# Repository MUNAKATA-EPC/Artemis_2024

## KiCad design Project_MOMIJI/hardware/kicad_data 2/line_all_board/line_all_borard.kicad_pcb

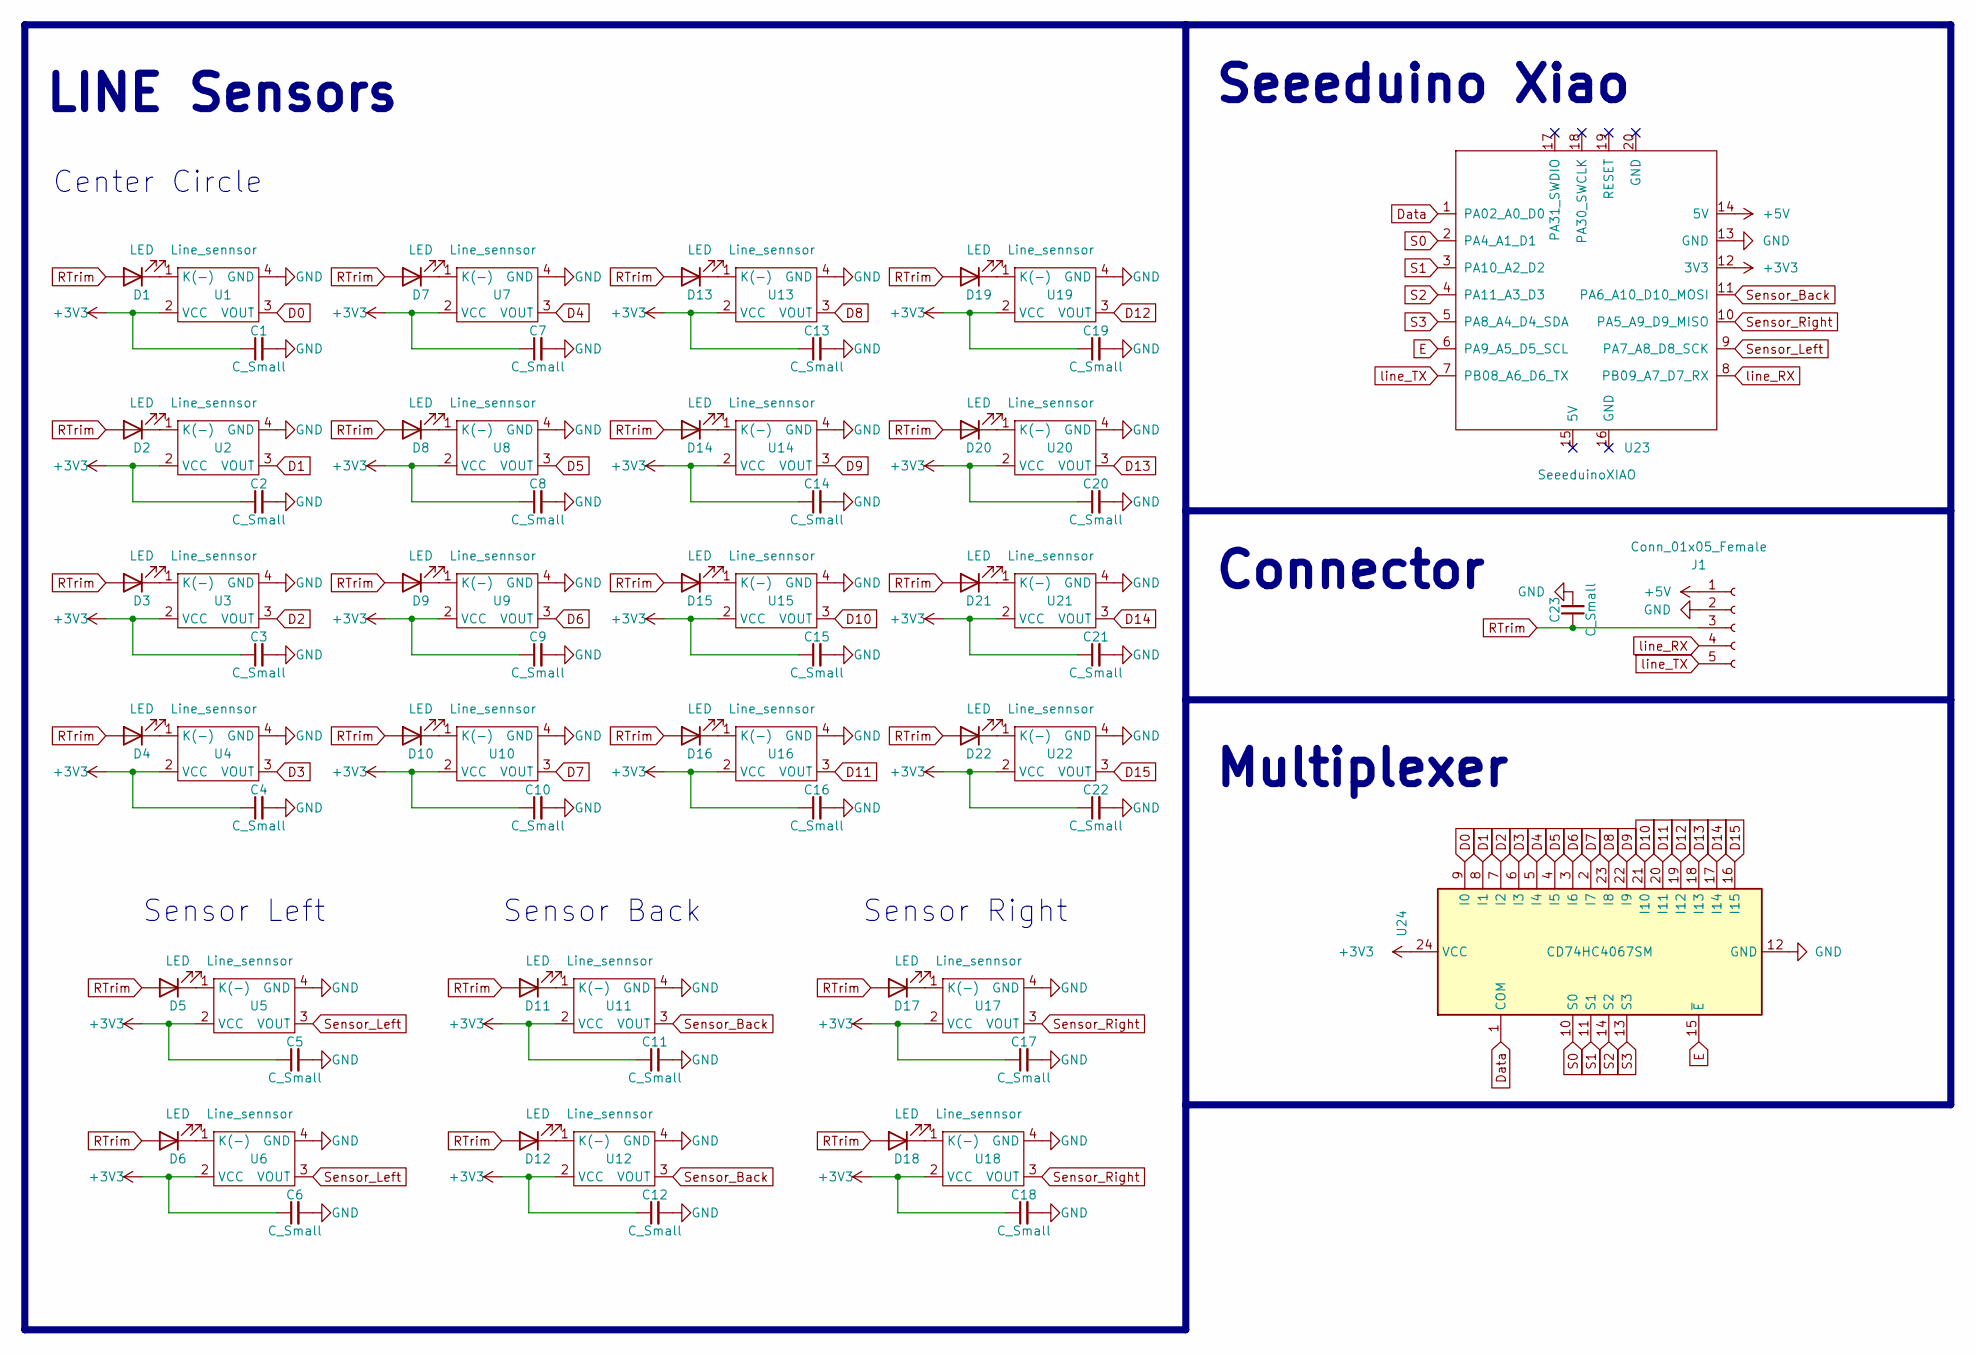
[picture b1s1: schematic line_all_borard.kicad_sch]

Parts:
C1, C2, C3, C4, C5, C6, C7, C8, C9, C10, C11, C12, C13, C14, C15, C16, C17, C18, C19, C20, C21, C22: C_Small; C_Disc_D3.4mm_W2.1mm_P2.50mm
C23: C_Small; CP_Radial_D5.0mm_P2.50mm
D1, D2, D3, D4, D5, D6, D7, D8, D9, D10, D11, D12, D13, D14, D15, D16, D17, D18, D19, D20, D21, D22: LED; LED_D3.0mm
J1: Conn_01x05_Female; JST_XH_B5B-XH-A_1x05_P2.50mm_Vertical
U1, U2, U3, U4, U5, U6, U7, U8, U9, U10, U11, U12, U13, U14, U15, U16, U17, U18, U19, U20, U21, U22: Line_sennsor; Line_Sensor_SMD
U23: SeeeduinoXIAO; seeeduinoXIAO
U24: CD74HC4067SM; SSOP-24_5.3x8.2mm_P0.65mm; LCSC C98457

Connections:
+3V3: C1.1, C2.1, C3.1, C4.1, C5.1, C6.1, C7.1, C8.1, C9.1, C10.1, C11.1, C12.1, C13.1, C14.1, C15.1, C16.1, C17.1, C18.1, C19.1, C20.1, C21.1, C22.1, U1.2 (VCC), U2.2 (VCC), U3.2 (VCC), U4.2 (VCC), U5.2 (VCC), U6.2 (VCC), U7.2 (VCC), U8.2 (VCC), U9.2 (VCC), U10.2 (VCC), U11.2 (VCC), U12.2 (VCC), U13.2 (VCC), U14.2 (VCC), U15.2 (VCC), U16.2 (VCC), U17.2 (VCC), U18.2 (VCC), U19.2 (VCC), U20.2 (VCC), U21.2 (VCC), U22.2 (VCC), U23.12 (3V3), U24.24 (VCC)
+5V: J1.1, U23.14 (5V)
D0: U1.3 (VOUT), U24.9 (I0)
D1: U2.3 (VOUT), U24.8 (I1)
D2: U3.3 (VOUT), U24.7 (I2)
D3: U4.3 (VOUT), U24.6 (I3)
D4: U7.3 (VOUT), U24.5 (I4)
D5: U8.3 (VOUT), U24.4 (I5)
D6: U9.3 (VOUT), U24.3 (I6)
D7: U10.3 (VOUT), U24.2 (I7)
D8: U13.3 (VOUT), U24.23 (I8)
D9: U14.3 (VOUT), U24.22 (I9)
D10: U15.3 (VOUT), U24.21 (I10)
D11: U16.3 (VOUT), U24.20 (I11)
D12: U19.3 (VOUT), U24.19 (I12)
D13: U20.3 (VOUT), U24.18 (I13)
D14: U21.3 (VOUT), U24.17 (I14)
D15: U22.3 (VOUT), U24.16 (I15)
Data: U23.1 (PA02_A0_D0), U24.1 (COM)
E: U23.6 (PA9_A5_D5_SCL), U24.15 (~E)
GND: C1.2, C2.2, C3.2, C4.2, C5.2, C6.2, C7.2, C8.2, C9.2, C10.2, C11.2, C12.2, C13.2, C14.2, C15.2, C16.2, C17.2, C18.2, C19.2, C20.2, C21.2, C22.2, C23.2, J1.2, U1.4 (GND), U2.4 (GND), U3.4 (GND), U4.4 (GND), U5.4 (GND), U6.4 (GND), U7.4 (GND), U8.4 (GND), U9.4 (GND), U10.4 (GND), U11.4 (GND), U12.4 (GND), U13.4 (GND), U14.4 (GND), U15.4 (GND), U16.4 (GND), U17.4 (GND), U18.4 (GND), U19.4 (GND), U20.4 (GND), U21.4 (GND), U22.4 (GND), U23.13 (GND), U24.12 (GND)
unnamed: D1.1 (K), U1.1 (K(-))
unnamed: D2.1 (K), U2.1 (K(-))
unnamed: D3.1 (K), U3.1 (K(-))
unnamed: D4.1 (K), U4.1 (K(-))
unnamed: D5.1 (K), U5.1 (K(-))
unnamed: D6.1 (K), U6.1 (K(-))
unnamed: D7.1 (K), U7.1 (K(-))
unnamed: D8.1 (K), U8.1 (K(-))
unnamed: D9.1 (K), U9.1 (K(-))
unnamed: D10.1 (K), U10.1 (K(-))
unnamed: D11.1 (K), U11.1 (K(-))
unnamed: D12.1 (K), U12.1 (K(-))
unnamed: D13.1 (K), U13.1 (K(-))
unnamed: D14.1 (K), U14.1 (K(-))
unnamed: D15.1 (K), U15.1 (K(-))
unnamed: D16.1 (K), U16.1 (K(-))
unnamed: D17.1 (K), U17.1 (K(-))
unnamed: D18.1 (K), U18.1 (K(-))
unnamed: D19.1 (K), U19.1 (K(-))
unnamed: D20.1 (K), U20.1 (K(-))
unnamed: D21.1 (K), U21.1 (K(-))
unnamed: D22.1 (K), U22.1 (K(-))
RTrim: C23.1, D1.2 (A), D2.2 (A), D3.2 (A), D4.2 (A), D5.2 (A), D6.2 (A), D7.2 (A), D8.2 (A), D9.2 (A), D10.2 (A), D11.2 (A), D12.2 (A), D13.2 (A), D14.2 (A), D15.2 (A), D16.2 (A), D17.2 (A), D18.2 (A), D19.2 (A), D20.2 (A), D21.2 (A), D22.2 (A), J1.3
S0: U23.2 (PA4_A1_D1), U24.10 (S0)
S1: U23.3 (PA10_A2_D2), U24.11 (S1)
S2: U23.4 (PA11_A3_D3), U24.14 (S2)
S3: U23.5 (PA8_A4_D4_SDA), U24.13 (S3)
Sensor_Back: U11.3 (VOUT), U12.3 (VOUT), U23.11 (PA6_A10_D10_MOSI)
Sensor_Left: U5.3 (VOUT), U6.3 (VOUT), U23.9 (PA7_A8_D8_SCK)
Sensor_Right: U17.3 (VOUT), U18.3 (VOUT), U23.10 (PA5_A9_D9_MISO)
line_RX: J1.4, U23.8 (PB09_A7_D7_RX)
line_TX: J1.5, U23.7 (PB08_A6_D6_TX)

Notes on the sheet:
Sensor Right
LINE Sensors
Center Circle
Sensor Left
Sensor Back
Seeeduino Xiao
Connector
Multiplexer

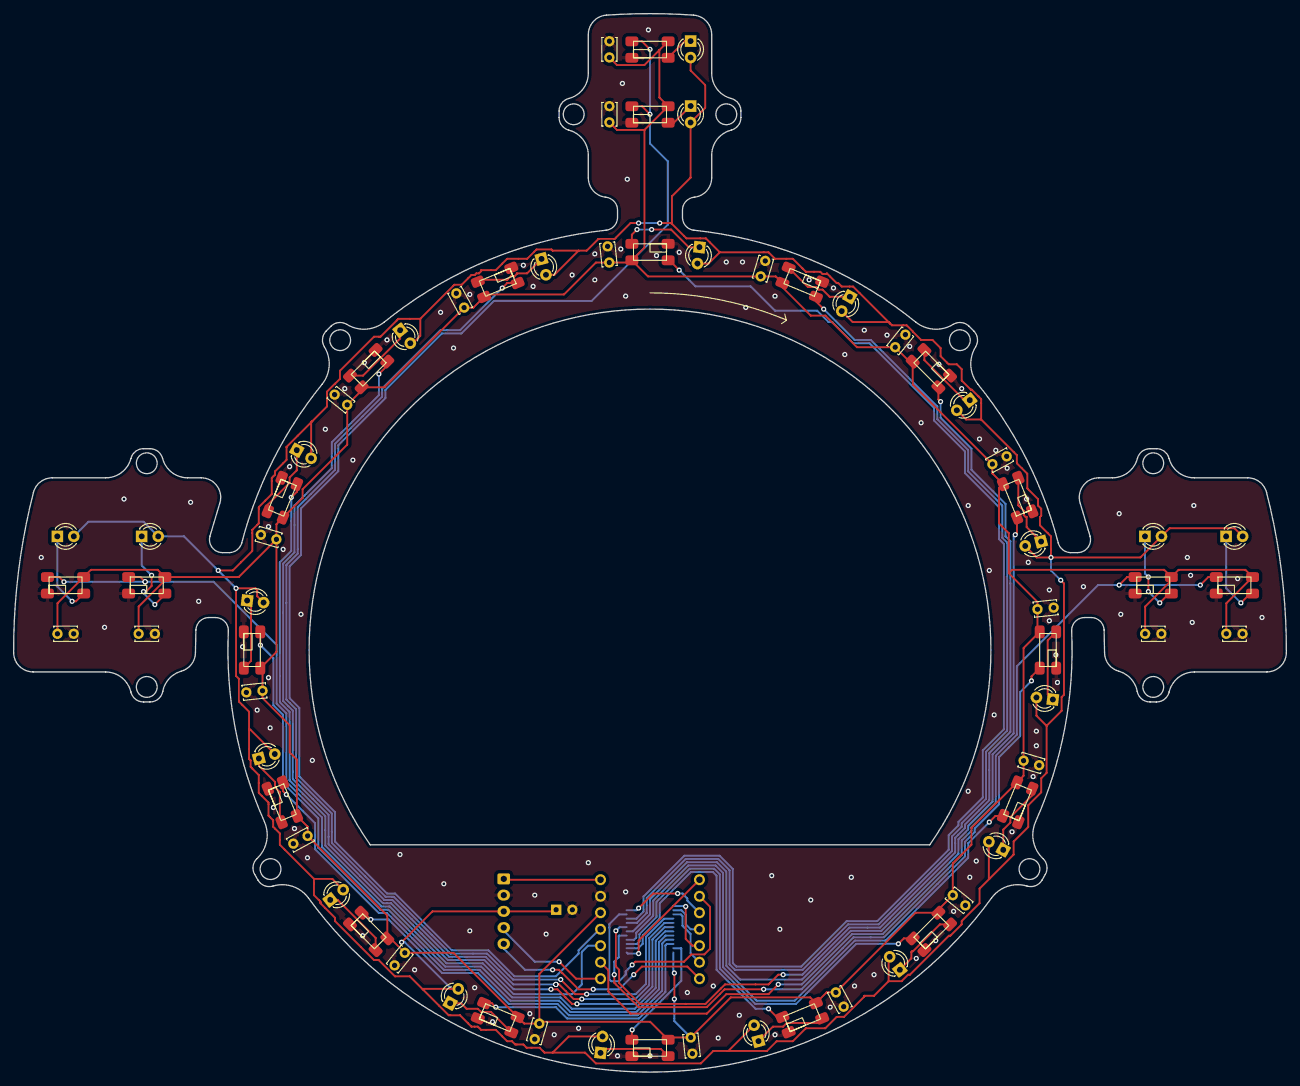
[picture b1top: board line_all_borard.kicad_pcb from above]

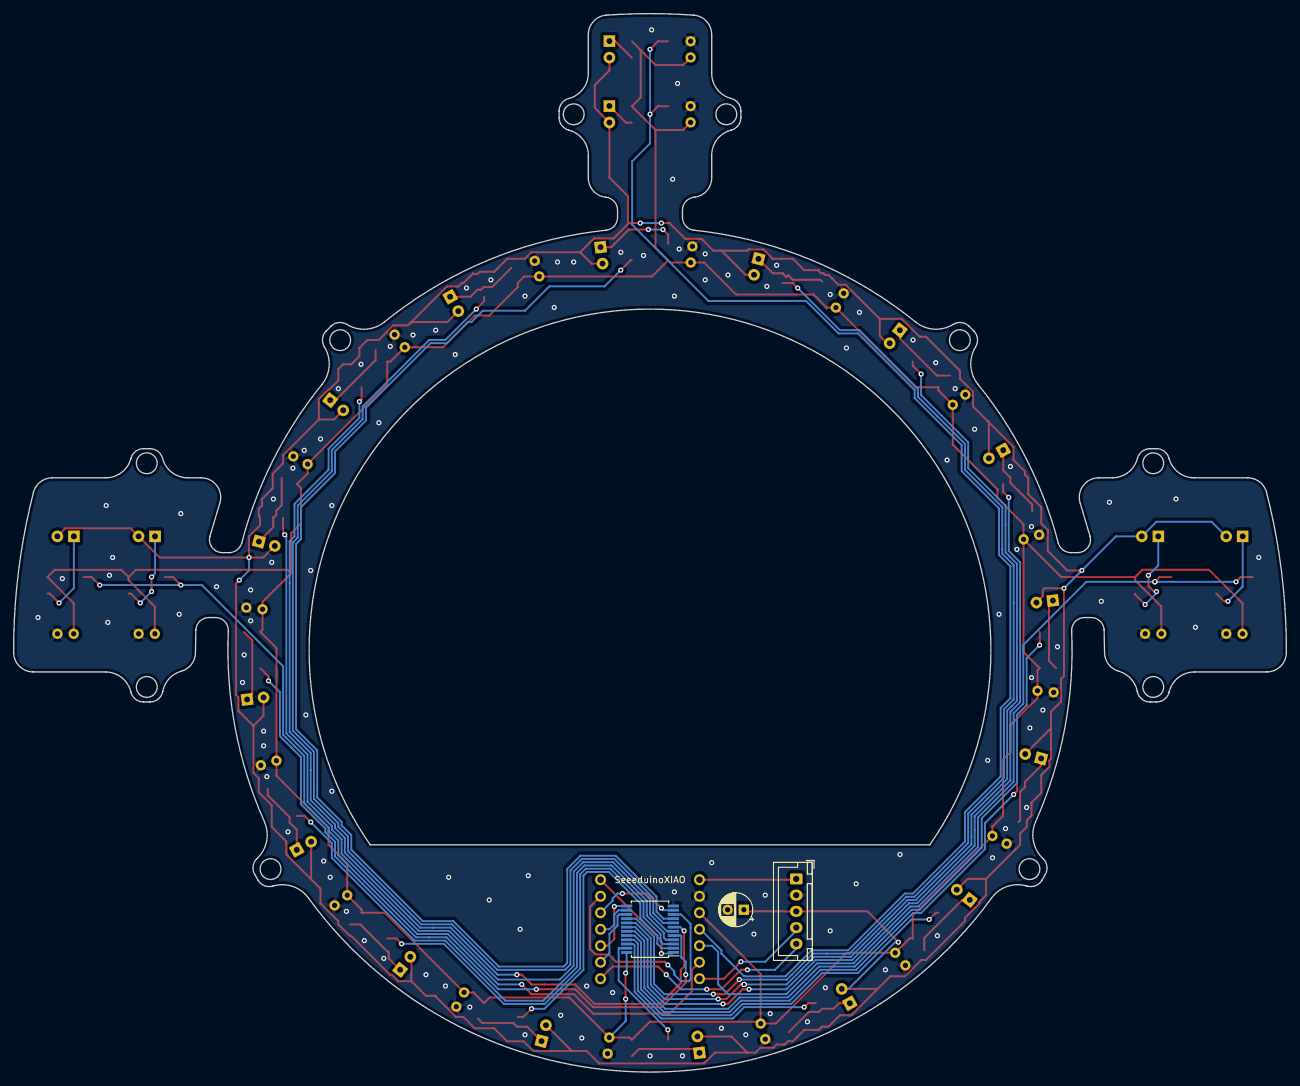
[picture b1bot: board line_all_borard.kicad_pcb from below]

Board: 2 copper layers, 196.0 x 163.0 mm, 70 parts (4 on the bottom side), 53 nets.

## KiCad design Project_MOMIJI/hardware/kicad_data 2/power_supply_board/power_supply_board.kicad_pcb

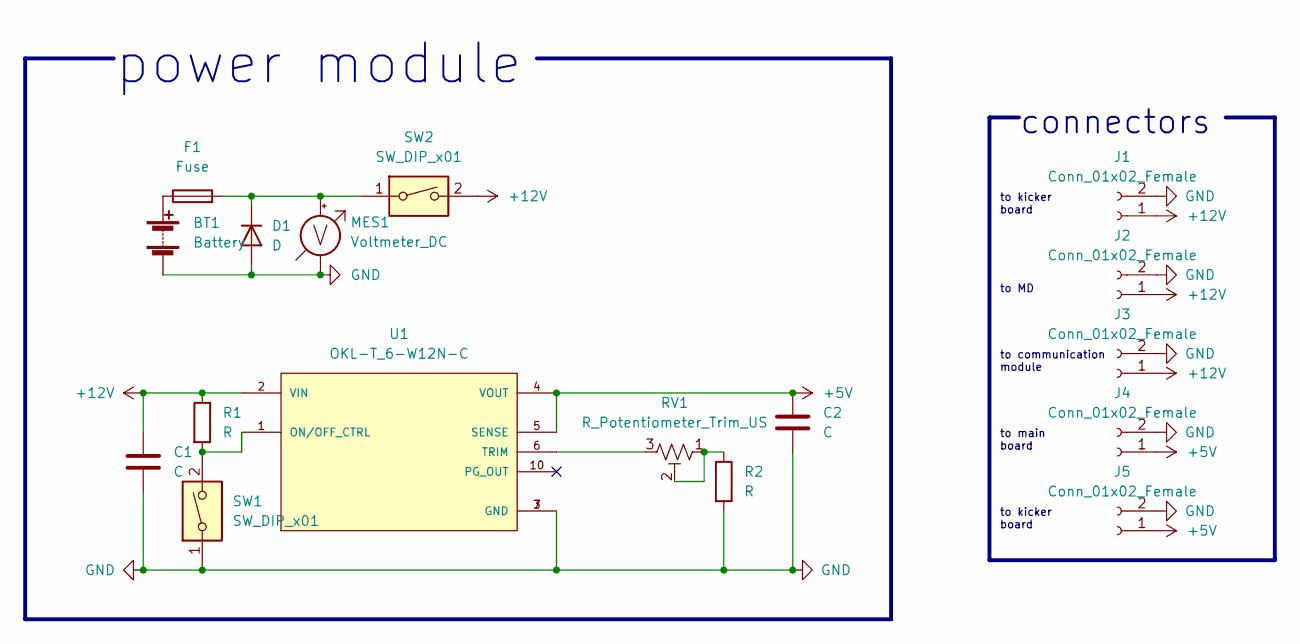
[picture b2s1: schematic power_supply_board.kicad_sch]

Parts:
BT1: Battery; JST_VH_B2P-VH_1x02_P3.96mm_Vertical
C1, C2: C; C_Disc_D4.7mm_W2.5mm_P5.00mm
D1: D; D_A-405_P10.16mm_Horizontal
F1: Fuse; fuse_socket
J1, J2, J3, J4, J5: Conn_01x02_Female; JST_XH_B2B-XH-A_1x02_P2.50mm_Vertical
MES1: Voltmeter_DC; voltage_counter
R1, R2: R; R_Axial_DIN0207_L6.3mm_D2.5mm_P7.62mm_Horizontal
RV1: R_Potentiometer_Trim_US; 2MS1T2B4M2QES
SW1: SW_DIP_x01; SW_S
SW2: SW_DIP_x01; DS-850k
U1: OKL-T_6-W12N-C; DCDC-murata-6A

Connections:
+5V: C2.1, J4.1, J5.1, U1.4 (VOUT), U1.5 (SENSE)
+12V: C1.1, J1.1, J2.1, J3.1, R1.1, SW2.2, U1.2 (VIN)
GND: BT1.2 (-), C1.2, C2.2, D1.2 (A), J1.2, J2.2, J3.2, J4.2, J5.2, MES1.1 (-), R2.2, SW1.1, U1.3 (GND), U1.7 (GND)
unnamed: BT1.1 (+), F1.1
unnamed: D1.1 (K), F1.2, MES1.2 (+), SW2.1
unnamed: R1.2, SW1.2, U1.1 (ON/OFF_CTRL)
unnamed: R2.1, RV1.1, RV1.2
unnamed: RV1.3, U1.6 (TRIM)

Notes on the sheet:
connectors
to communication module
to main board
to MD
to kicker board
power module

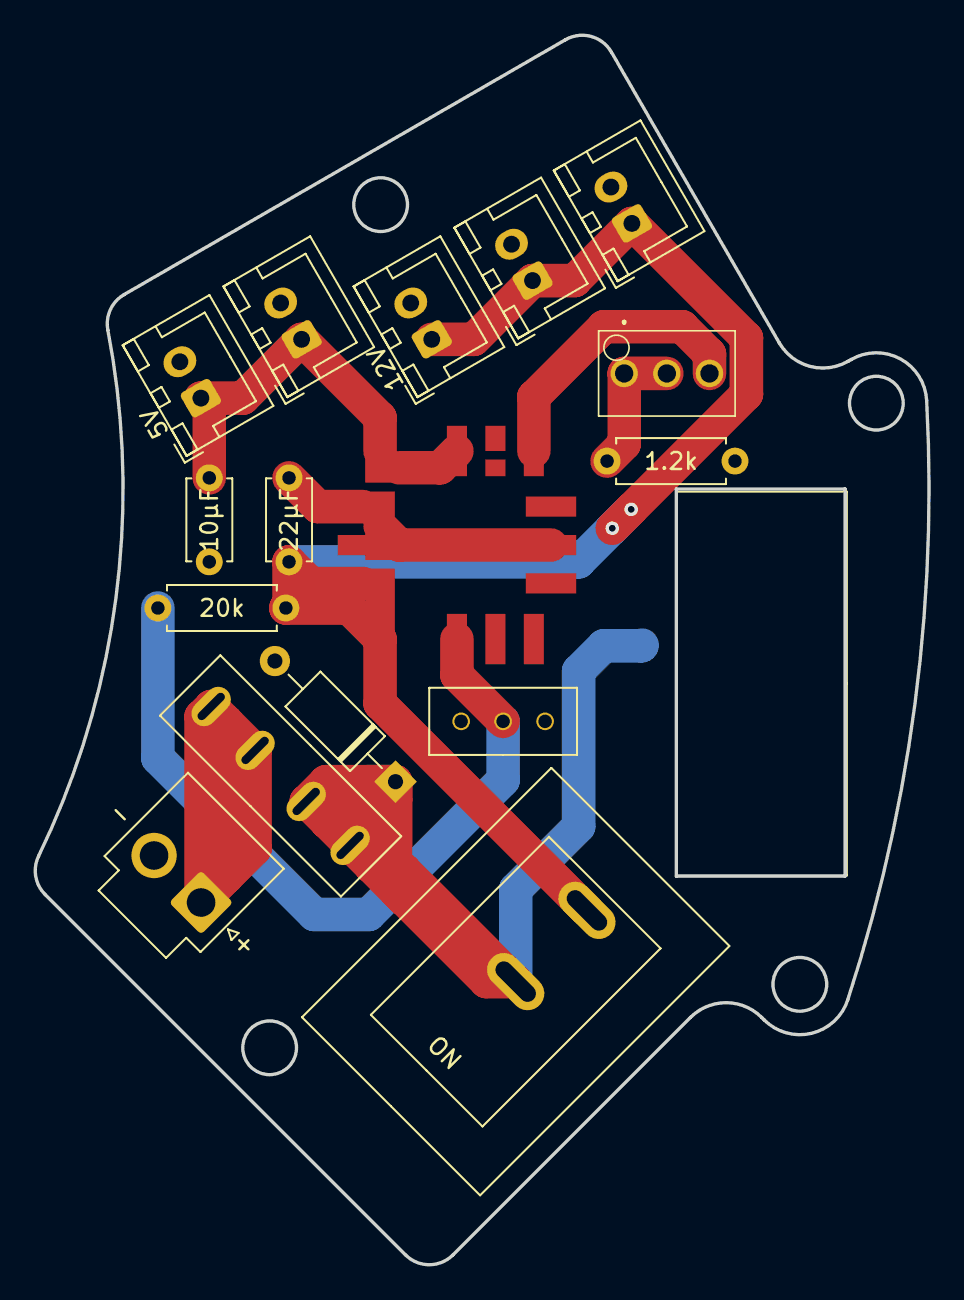
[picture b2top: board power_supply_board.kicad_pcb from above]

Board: 2 copper layers, 53.2 x 73.2 mm, 17 parts (0 on the bottom side), 8 nets.

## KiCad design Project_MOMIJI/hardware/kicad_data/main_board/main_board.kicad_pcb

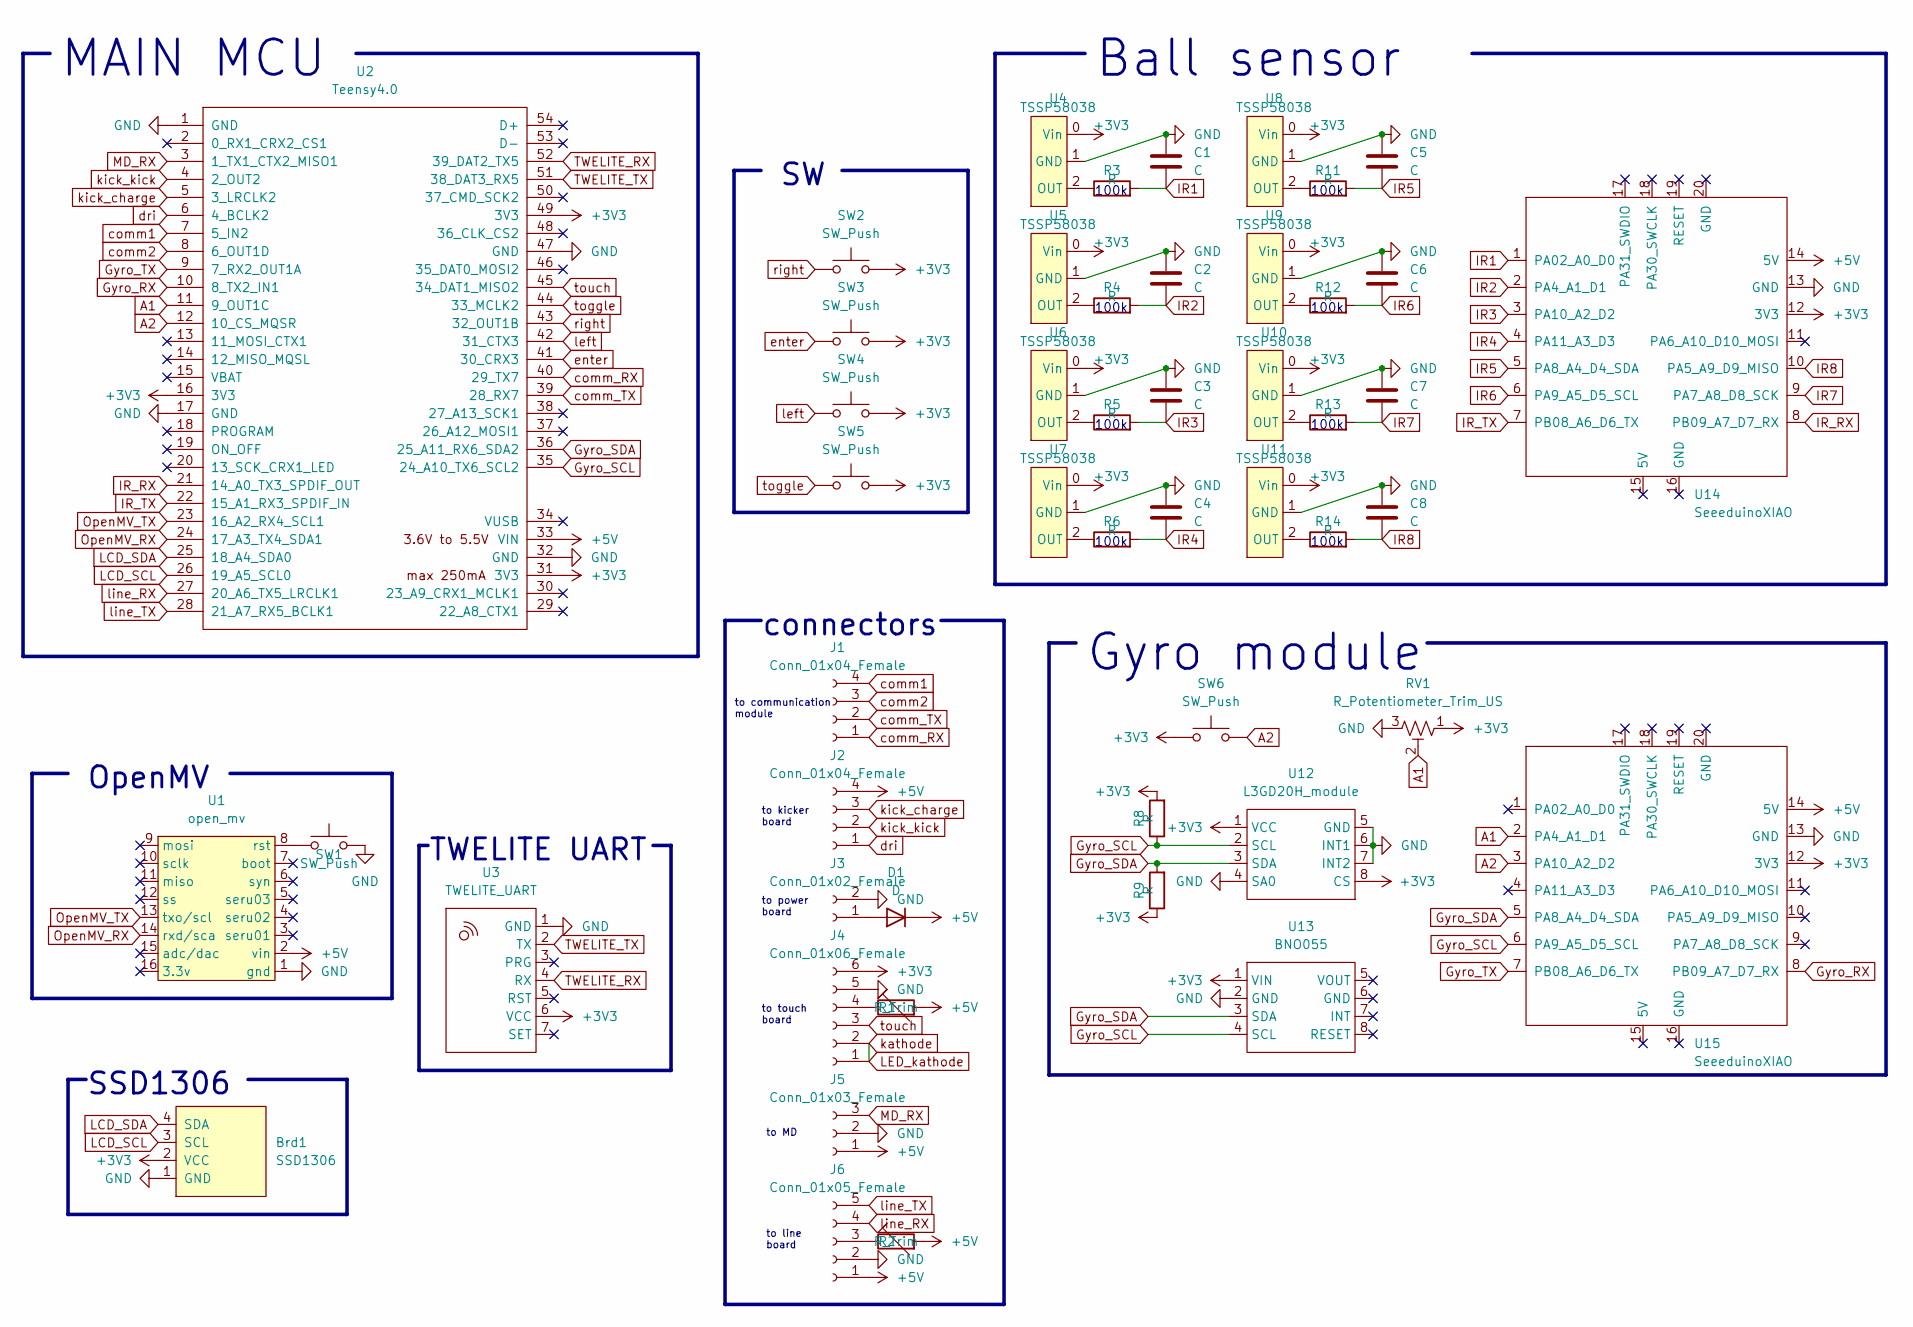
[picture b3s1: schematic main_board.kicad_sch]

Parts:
Brd1: SSD1306; PinSocket_1x04_P2.54mm_Vertical
C1, C2, C3, C4, C5, C6, C7, C8: C; C_Disc_D3.4mm_W2.1mm_P2.50mm
D1: D; D_5W_P12.70mm_Horizontal
J1, J2: Conn_01x04_Female; JST_XH_B4B-XH-A_1x04_P2.50mm_Vertical
J3: Conn_01x02_Female; JST_XH_B2B-XH-A_1x02_P2.50mm_Vertical
J4: Conn_01x06_Female; JST_XH_B6B-XH-A_1x06_P2.50mm_Vertical
J5: Conn_01x03_Female; JST_XH_B3B-XH-A_1x03_P2.50mm_Vertical
J6: Conn_01x05_Female; JST_XH_B5B-XH-A_1x05_P2.50mm_Vertical
R1, R2: R_Trim; 可変抵抗
R3, R4, R5, R6, R8, R9, R11, R12, R13, R14: R; R_Axial_DIN0207_L6.3mm_D2.5mm_P7.62mm_Horizontal
RV1: R_Potentiometer_Trim_US; 可変抵抗
SW1, SW2, SW3, SW4: SW_Push; SW_PUSH_6mm_H7.3mm
SW5: SW_Push; PinHeader_1x02_P2.54mm_Vertical
SW6: SW_Push; SW
U1: open_mv; OpenMV
U2: Teensy4.0; Teensy_Brakeout
U3: TWELITE_UART; TWELITE UART
U4, U5, U6, U7, U8, U9, U10, U11: TSSP58038
U12: L3GD20H_module; L3GD20H_Module_KiCad6.0
U13: BNO055
U14, U15: SeeeduinoXIAO; seeeduinoXIAO

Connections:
+3V3: Brd1.2 (VCC), J4.6, R8.2, R9.1, RV1.1, SW2.2, SW3.2, SW4.2, SW5.2, SW6.1, U2.16 (3V3), U2.31 (3V3), U2.49 (3V3), U3.6 (VCC), U4.0 (Vin), U5.0 (Vin), U6.0 (Vin), U7.0 (Vin), U8.0 (Vin), U9.0 (Vin), U10.0 (Vin), U11.0 (Vin), U12.1 (VCC), U12.8 (CS), U13.1 (VIN), U14.12 (3V3), U15.12 (3V3)
+5V: D1.1 (K), J2.4, J5.1, J6.1, R1.2, R2.2, U1.2 (vin), U2.33 (VIN), U14.14 (5V), U15.14 (5V)
A1: RV1.2, U2.11 (9_OUT1C), U15.2 (PA4_A1_D1)
A2: SW6.2, U2.12 (10_CS_MQSR), U15.3 (PA10_A2_D2)
GND: Brd1.1 (GND), C1.1, C2.1, C3.1, C4.1, C5.1, C6.1, C7.1, C8.1, J3.2, J4.5, J5.2, J6.2, RV1.3, SW1.2, U1.1 (gnd), U2.1 (GND), U2.17 (GND), U2.32 (GND), U2.47 (GND), U3.1 (GND), U4.1 (GND), U5.1 (GND), U6.1 (GND), U7.1 (GND), U8.1 (GND), U9.1 (GND), U10.1 (GND), U11.1 (GND), U12.4 (SA0), U12.5 (GND), U12.6 (INT1), U12.7 (INT2), U13.2 (GND), U14.13 (GND), U15.13 (GND)
Gyro_RX: U2.10 (8_TX2_IN1), U15.8 (PB09_A7_D7_RX)
Gyro_SCL: R8.1, U2.35 (24_A10_TX6_SCL2), U12.2 (SCL), U13.4 (SCL), U15.6 (PA9_A5_D5_SCL)
Gyro_SDA: R9.2, U2.36 (25_A11_RX6_SDA2), U12.3 (SDA), U13.3 (SDA), U15.5 (PA8_A4_D4_SDA)
Gyro_TX: U2.9 (7_RX2_OUT1A), U15.7 (PB08_A6_D6_TX)
IR1: C1.2, R3.2, U14.1 (PA02_A0_D0)
IR2: C2.2, R4.2, U14.2 (PA4_A1_D1)
IR3: C3.2, R5.2, U14.3 (PA10_A2_D2)
IR4: C4.2, R6.2, U14.4 (PA11_A3_D3)
IR5: C5.2, R11.2, U14.5 (PA8_A4_D4_SDA)
IR6: C6.2, R12.2, U14.6 (PA9_A5_D5_SCL)
IR7: C7.2, R13.2, U14.9 (PA7_A8_D8_SCK)
IR8: C8.2, R14.2, U14.10 (PA5_A9_D9_MISO)
IR_RX: U2.21 (14_A0_TX3_SPDIF_OUT), U14.8 (PB09_A7_D7_RX)
IR_TX: U2.22 (15_A1_RX3_SPDIF_IN), U14.7 (PB08_A6_D6_TX)
LCD_SCL: Brd1.3 (SCL), U2.26 (19_A5_SCL0)
LCD_SDA: Brd1.4 (SDA), U2.25 (18_A4_SDA0)
LED_kathode: J4.1, J4.2
MD_RX: J5.3, U2.3 (1_TX1_CTX2_MISO1)
unnamed: D1.2 (A), J3.1
unnamed: J4.4, R1.1
unnamed: J6.3, R2.1
unnamed: R3.1, U4.2 (OUT)
unnamed: R4.1, U5.2 (OUT)
unnamed: R5.1, U6.2 (OUT)
unnamed: R6.1, U7.2 (OUT)
unnamed: R11.1, U8.2 (OUT)
unnamed: R12.1, U9.2 (OUT)
unnamed: R13.1, U10.2 (OUT)
unnamed: R14.1, U11.2 (OUT)
unnamed: SW1.1, U1.8 (rst)
OpenMV_RX: U1.14 (rxd/sca), U2.24 (17_A3_TX4_SDA1)
OpenMV_TX: U1.13 (txo/scl), U2.23 (16_A2_RX4_SCL1)
TWELITE_RX: U2.52 (39_DAT2_TX5), U3.4 (RX)
TWELITE_TX: U2.51 (38_DAT3_RX5), U3.2 (TX)
comm1: J1.4, U2.7 (5_IN2)
comm2: J1.3, U2.8 (6_OUT1D)
comm_RX: J1.1, U2.40 (29_TX7)
comm_TX: J1.2, U2.39 (28_RX7)
dri: J2.1, U2.6 (4_BCLK2)
enter: SW3.1, U2.41 (30_CRX3)
kick_charge: J2.3, U2.5 (3_LRCLK2)
kick_kick: J2.2, U2.4 (2_OUT2)
left: SW4.1, U2.42 (31_CTX3)
line_RX: J6.4, U2.27 (20_A6_TX5_LRCLK1)
line_TX: J6.5, U2.28 (21_A7_RX5_BCLK1)
right: SW2.1, U2.43 (32_OUT1B)
toggle: SW5.1, U2.44 (33_MCLK2)
touch: J4.3, U2.45 (34_DAT1_MISO2)

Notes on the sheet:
100k
connectors
to MD
TWELITE UART
to kicker board
to power board
to communication module
to line board
SSD1306
OpenMV
Gyro module
Ball sensor
MAIN MCU
to touch board

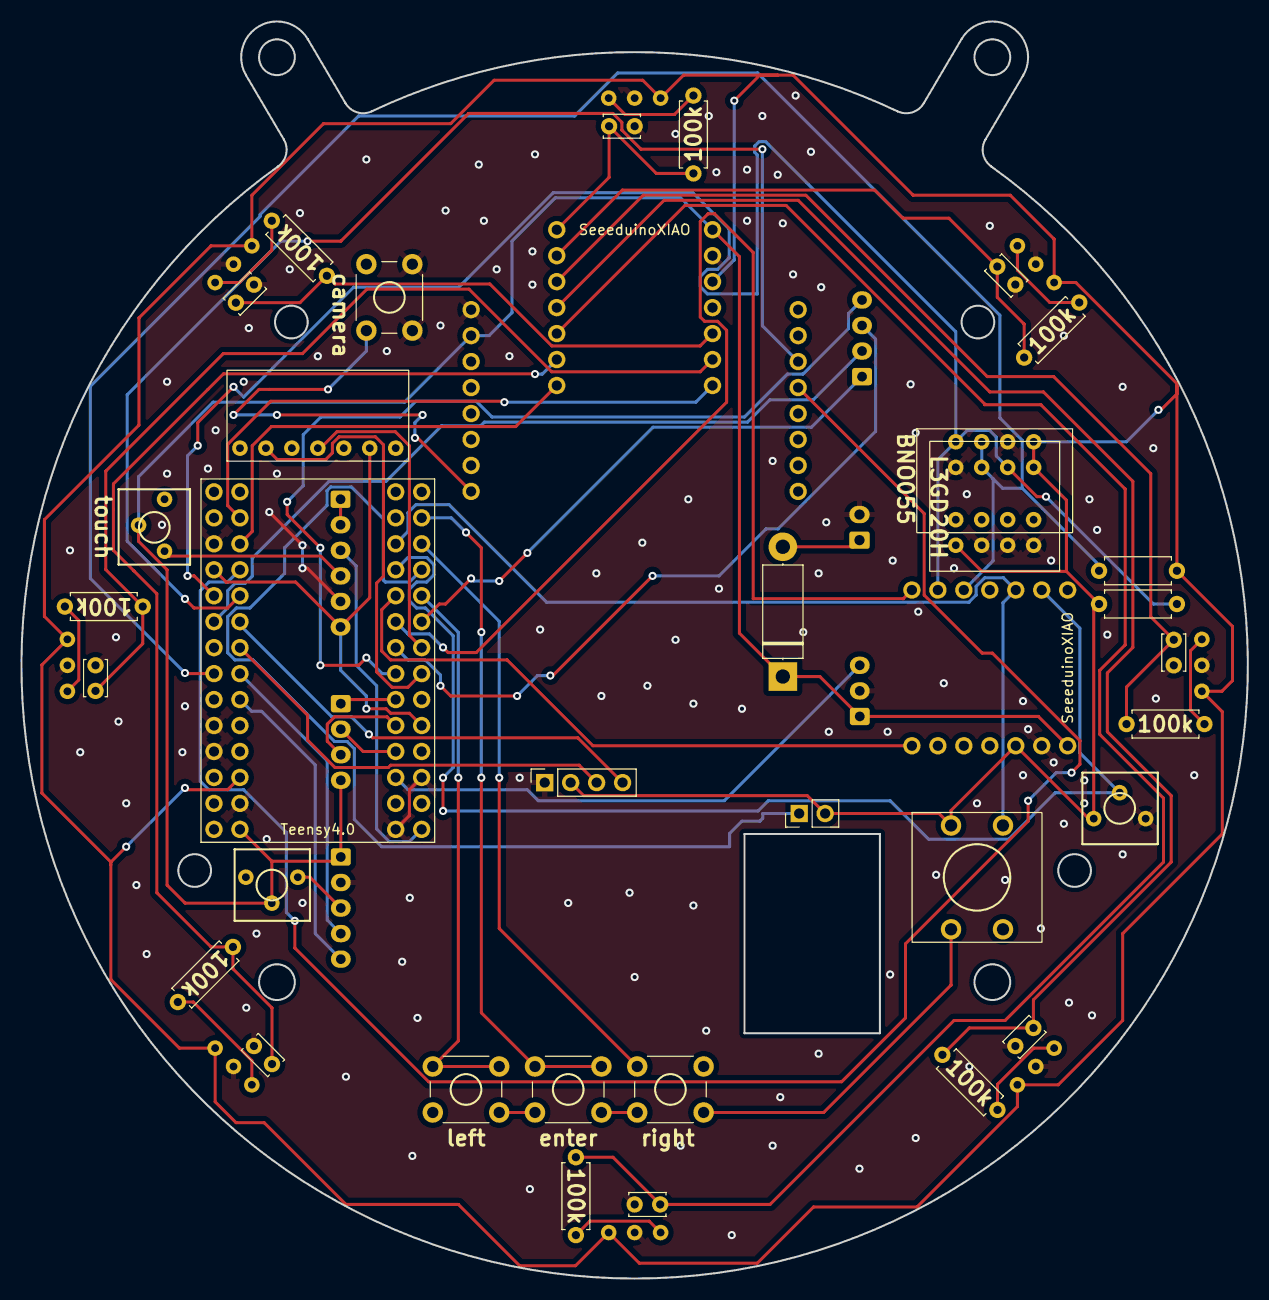
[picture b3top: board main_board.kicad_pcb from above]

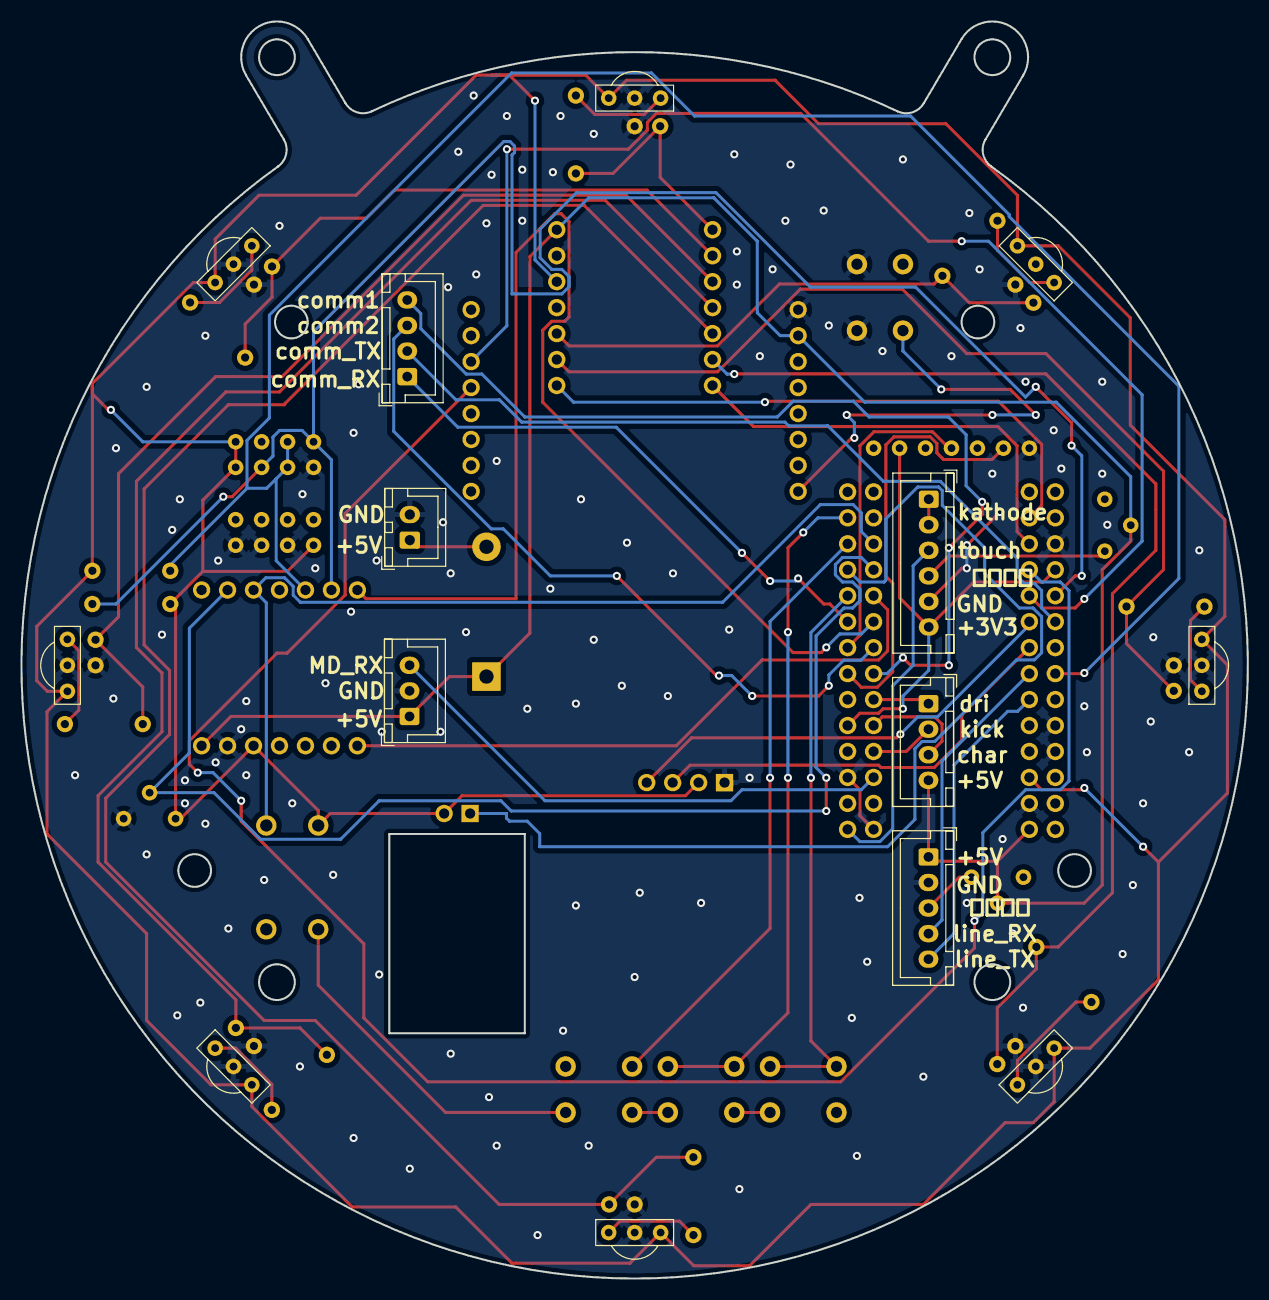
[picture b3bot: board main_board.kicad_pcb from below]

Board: 2 copper layers, 120.0 x 123.0 mm, 50 parts (15 on the bottom side), 53 nets.
